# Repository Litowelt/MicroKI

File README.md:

# MicroKI

Das "MicroKI" ist ein Projekt, das sich mit digitalen Zusatzanzeigen befasst. Das MicroKI ermöglicht den Anschluss von bis zu 6 Zusatzanzeigen (0.96" OLED LCDs) an ein System. Die Daten für diese Anzeigen können entweder über den CAN-Bus (1x) oder über externe Sensor-Eingänge bezogen werden. Es stehen verschiedene externe Sensor-Eingänge zur Verfügung, darunter Batterie Spannung und Öldruck. Jede der 6 Anzeigen kann separat angesteuert werden und die Daten können über Tasten auf der Platine oder externe Tasten umgeschaltet werden.

# Anschluss Übersicht
Digitale Zusatzanzeigen (0.96" OLED LCDs):

- Bis zu 6 dieser Displays können an das MicroKI angeschlossen werden.

Datenquelle:

- Die Daten können über den CAN-Bus (1x) oder über externe Sensor-Eingänge bezogen werden.
  
Externe Sensor-Eingänge:

- 1x Batterie Spannung
- 1x Öldruck Sensor (VDO)
  
Steuerung und Umschaltung:

- Alle 6 Anzeigen können separat angesteuert werden.
- Die Umschaltung zwischen den Anzeigen und die Steuerung erfolgen entweder über die Buttons auf der Platine oder über externe Buttons.

# Unterstütze Fahrzeuge und Nachrichten

- VW T5.1
  - Öl Temperatur (wenn der Sensor verbaut ist) - ✓
  - Kühlwasser Temperatur - ✓
  - Ladeluft Temperatur - ✓
  - Außentemperatur (wenn der Sensor verbaut ist) - ✓
  - Ladedruck - ✓
 
- Universal (Analoge Eingänge)
  - Öl Temperatur - X
  - Kühlwasser Temperatur - X
  - Außentemperatur - X
  - Öldruck - X
  - Ladedruck - X
 
# ToDo
- Code fertig schreiben. - in Arbeit
- Prototypen V2 bauen (Bauteile und Platinen sind bestellt).
- CAN Nachrichten für T5.2 heraus finden. - Müssen nur noch final getestet werden
- CAN Support für Haltech ECU hinzufügen - in Arbeit
- CAN Support für Ecumaster EMU ECU hinzufügen - in Arbeit
- CAN Support für Maxx ECU hinzufügen - in Arbeit

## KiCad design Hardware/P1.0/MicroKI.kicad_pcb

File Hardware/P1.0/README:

This is just a prototype! I make no guarantees that it works. Use at your own risk!

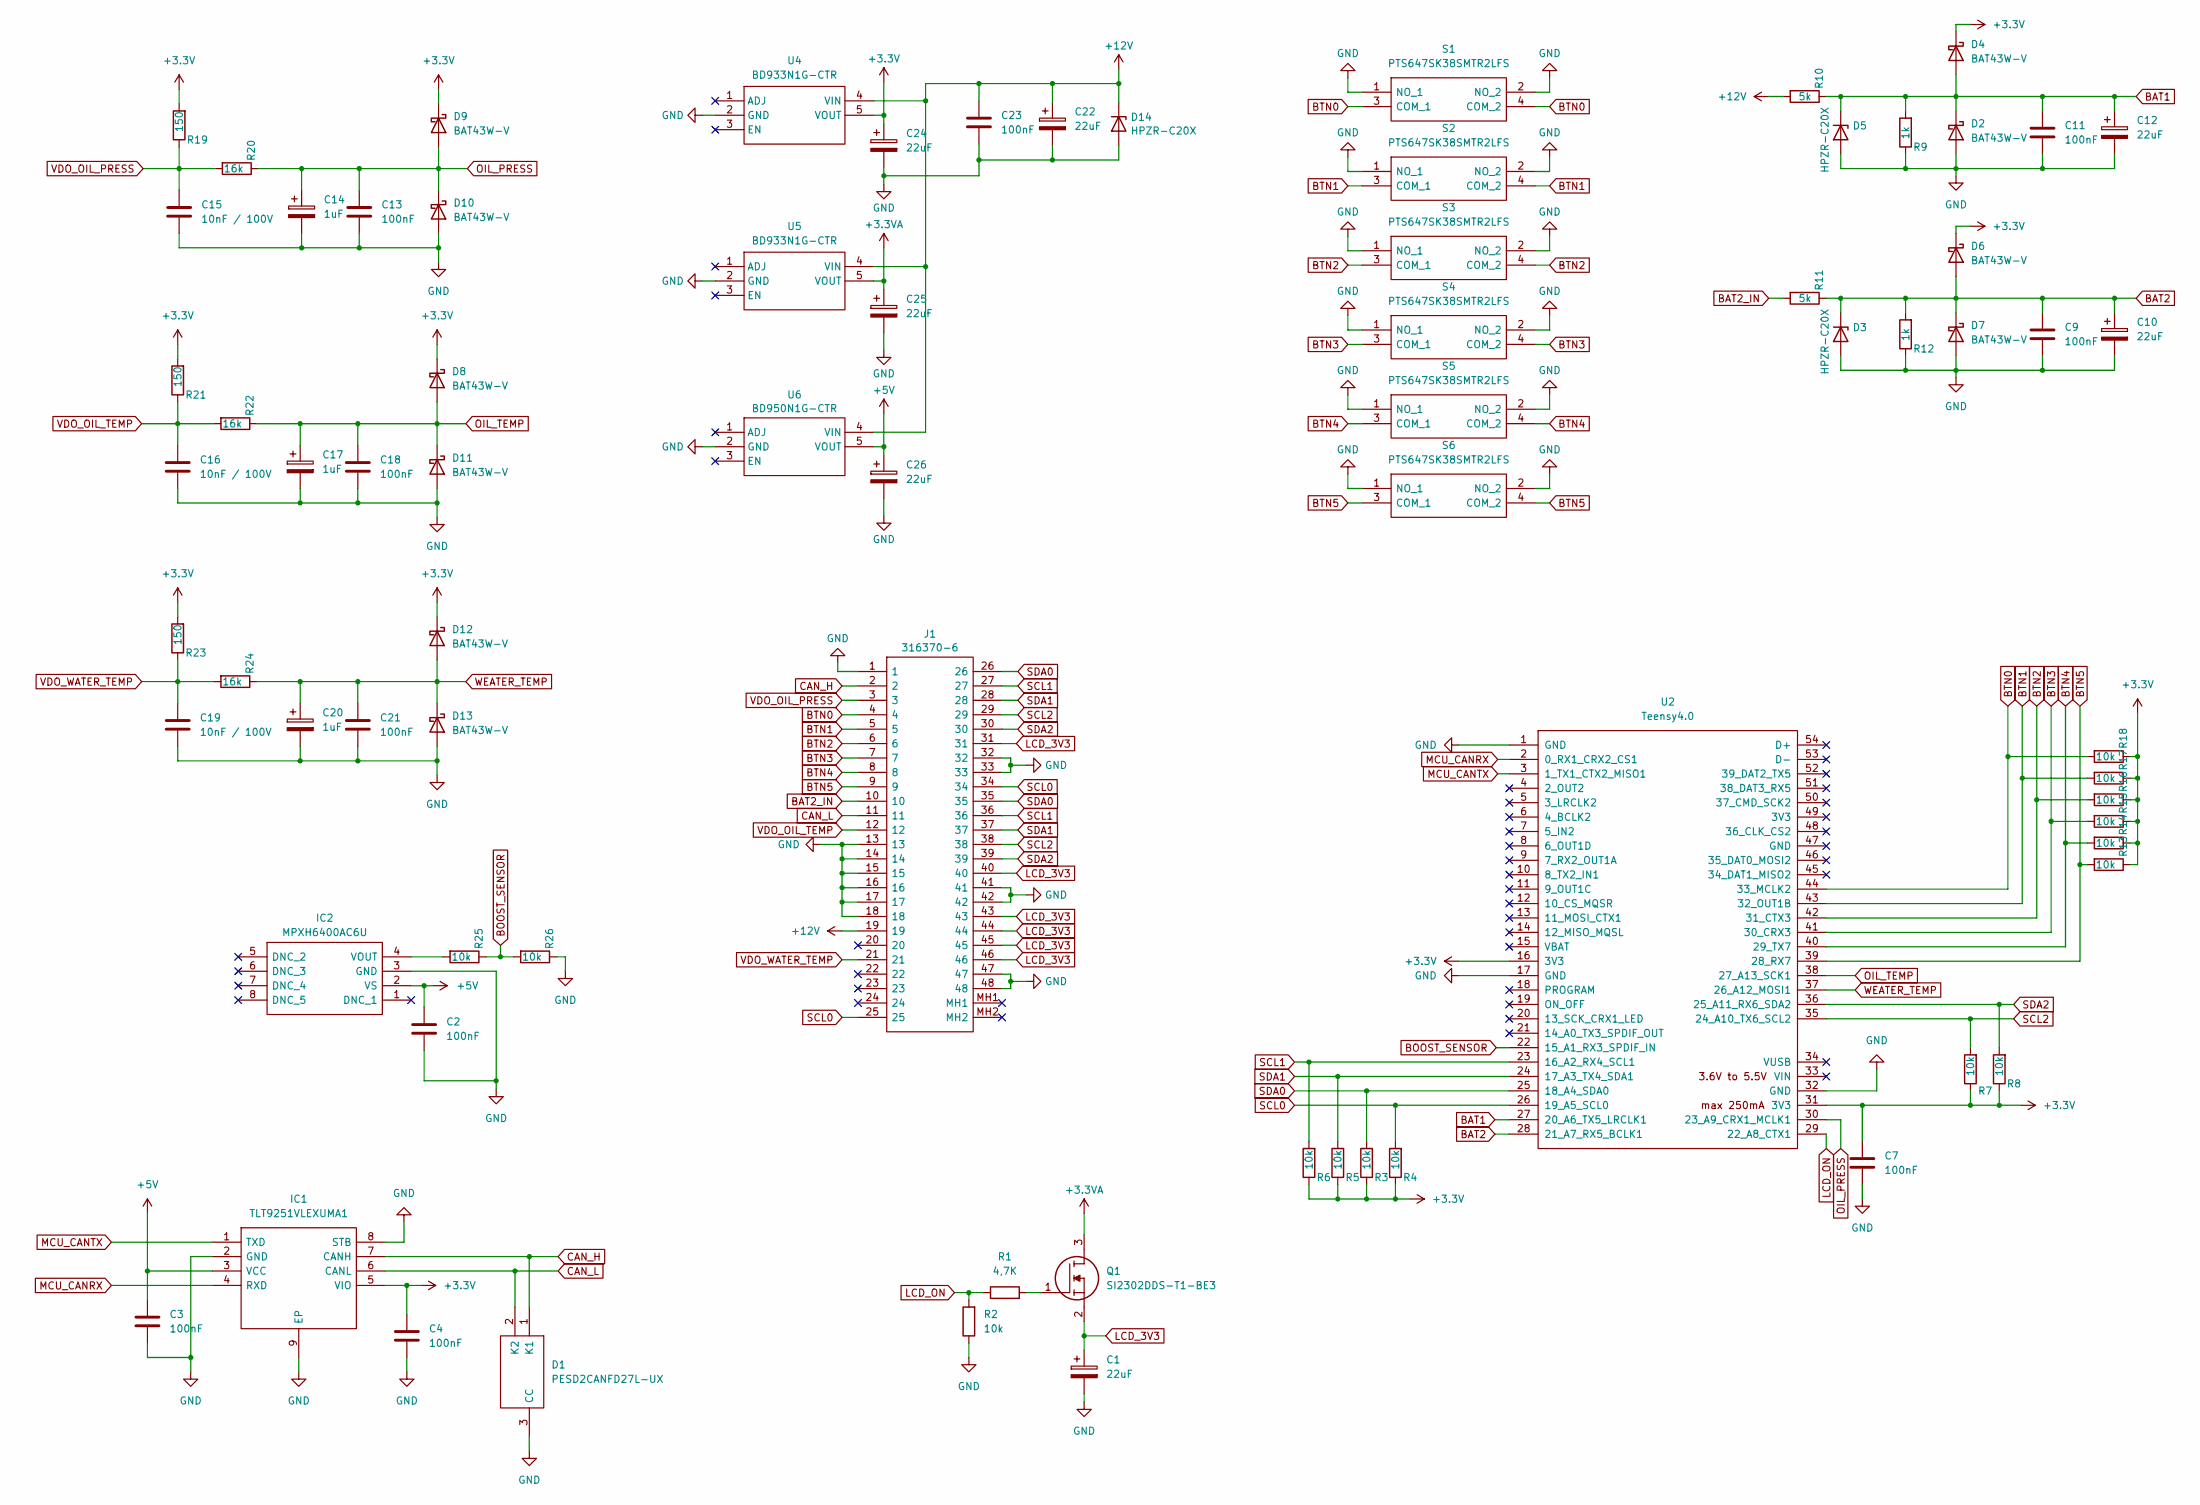
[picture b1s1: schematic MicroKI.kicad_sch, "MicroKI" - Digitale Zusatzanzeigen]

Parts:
C1, C10, C12, C22, C24, C25, C26: 22uF; CP_Elec_5x5.4; Manufacturer_Part_Number 865080442004; Mouser Part Number 710-865080442004
C2, C3, C4, C7, C9, C11, C13, C18, C21, C23: 100nF; C_0805_2012Metric_Pad1.18x1.45mm_HandSolder; Manufacturer_Part_Number C0805C104M5RAC7025; Mouser Part Number 80-C0805C104M5RACTM
C14, C17, C20: 1uF; CP_Elec_4x5.7; Manufacturer_Part_Number 865060640001; Mouser Part Number 710-865060640001
C15, C16, C19: 10nF / 100V; C_0603_1608Metric_Pad1.08x0.95mm_HandSolder; Manufacturer_Part_Number GCM188R72A103KA37J; Mouser Part Number 81-GCM188R72A103KA7J
D1: PESD2CANFD27L-UX; SOT65P210X110-3N; Mouser Part Number 771-PESD2CANFD27L-UX
D2, D4, D6, D7, D8, D9, D10, D11, D12, D13: BAT43W-V; D_SOD-123; Manufacturer_Part_Number BAT43W-G3-08; Mouser Part Number 78-BAT43W-G3-08
D3, D5, D14: HPZR-C20X; HPZRC20X; Manufacturer_Part_Number HPZR-C20X; Mouser Part Number 771-HPZR-C20X
IC1: TLT9251VLEXUMA1; SON65P300X300X110-9N; Manufacturer_Part_Number TLT9251VLEXUMA1; Mouser Part Number 726-TLT9251VLEXUMA1
IC2: MPXH6400AC6U; MPXH6115AC6U; Mouser Part Number 841-MPXH6400AC6U
J1: 316370-6; 3163706; Mouser Part Number 571-316370-6
Q1: SI2302DDS-T1-BE3; SOT95P237X112-3N; Mouser Part Number 78-SI2302DDS-T1-BE3
R1: 4,7K; R_0805_2012Metric_Pad1.20x1.40mm_HandSolder; Manufacturer_Part_Number RK73B2ATTD472J; Mouser Part Number 660-RK73B2ATTD472J
R2, R3, R4, R5, R6, R7, R8, R13, R14, R15, R16, R17, R18, R25, R26: 10k; R_0805_2012Metric_Pad1.20x1.40mm_HandSolder; Manufacturer_Part_Number RC0805FR-1010KL; Mouser Part Number 603-RC0805FR-1010KL
R9, R12: 1k; R_0805_2012Metric_Pad1.20x1.40mm_HandSolder; Manufacturer_Part_Number ERJ-P06D1001V; Mouser Part Number 667-ERJ-P06D1001V
R10, R11: 5k; R_0805_2012Metric_Pad1.20x1.40mm_HandSolder; Manufacturer_Part_Number CRCW08055K00FKTA; Mouser Part Number 71-CRCW0805-5K
R19, R21, R23: 150; R_0805_2012Metric_Pad1.20x1.40mm_HandSolder; Manufacturer_Part_Number ERJ-P06D1500V; Mouser Part Number 667-ERJ-P06D1500V
R20, R22, R24: 16k; R_0805_2012Metric_Pad1.20x1.40mm_HandSolder; Manufacturer_Part_Number RC0805FR-0716KL; Mouser Part Number 603-RC0805FR-0716KL
S1, S2, S3, S4, S5, S6: PTS647SK38SMTR2LFS; Mouser Part Number 611-PTS647SK38SMTR2L
U2: Teensy4.0; Teensy40_SMT
U4, U5: BD933N1G-CTR; BD9xxN1WG-CTR; Manufacturer_Part_Number BD933N1G-CTR; Mouser Part Number 755-BD933N1G-CTR
U6: BD950N1G-CTR; BD9xxN1WG-CTR; Manufacturer_Part_Number BD950N1G-CTR; Mouser Part Number 755-BD950N1G-CTR

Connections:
+3.3V: C4.1, C7.1, C24.1, D4.1 (K), D6.1 (K), D8.1 (K), D9.1 (K), D12.1 (K), IC1.5 (VIO), R3.1, R4.1, R5.1, R6.1, R7.1, R8.1, R13.1, R14.1, R15.1, R16.1, R17.1, R18.1, R19.2, R21.2, R23.2, U2.16 (3V3), U2.31 (3V3), U4.5 (VOUT)
+3.3VA: C25.1, Q1.3, U5.5 (VOUT)
+5V: C2.1, C3.1, C26.1, IC1.3 (VCC), IC2.2 (VS), U6.5 (VOUT)
+12V: C22.1, C23.1, D14.1 (K), J1.19, R10.2, U4.4 (VIN), U5.4 (VIN), U6.4 (VIN)
BAT1: C11.1, C12.1, D2.1 (K), D4.2 (A), D5.1 (K), R9.2, R10.1, U2.27 (20_A6_TX5_LRCLK1)
BAT2: C9.1, C10.1, D3.1 (K), D6.2 (A), D7.1 (K), R11.1, R12.2, U2.28 (21_A7_RX5_BCLK1)
BAT2_IN: J1.10, R11.2
BOOST_SENSOR: R25.1, R26.2, U2.22 (15_A1_RX3_SPDIF_IN)
BTN0: J1.4, R18.2, S1.3 (COM_1), S1.4 (COM_2), U2.44 (33_MCLK2)
BTN1: J1.5, R17.2, S2.3 (COM_1), S2.4 (COM_2), U2.43 (32_OUT1B)
BTN2: J1.6, R16.2, S3.3 (COM_1), S3.4 (COM_2), U2.42 (31_CTX3)
BTN3: J1.7, R15.2, S4.3 (COM_1), S4.4 (COM_2), U2.41 (30_CRX3)
BTN4: J1.8, R14.2, S5.3 (COM_1), S5.4 (COM_2), U2.40 (29_TX7)
BTN5: J1.9, R13.2, S6.3 (COM_1), S6.4 (COM_2), U2.39 (28_RX7)
CAN_H: D1.1 (K1), IC1.7 (CANH), J1.2
CAN_L: D1.2 (K2), IC1.6 (CANL), J1.11
GND: C1.2, C2.2, C3.2, C4.2, C7.2, C9.2, C10.2, C11.2, C12.2, C13.2, C14.2, C15.2, C16.2, C17.2, C18.2, C19.2, C20.2, C21.2, C22.2, C23.2, C24.2, C25.2, C26.2, D1.3 (CC), D2.2 (A), D3.2 (A), D5.2 (A), D7.2 (A), D10.2 (A), D11.2 (A), D13.2 (A), D14.2 (A), IC1.2 (GND), IC1.8 (STB), IC1.9 (EP), IC2.3 (GND), J1.1, J1.13, J1.14, J1.15, J1.16, J1.17, J1.18, J1.32, J1.33, J1.41, J1.42, J1.47, J1.48, R2.1, R9.1, R12.1, R26.1, S1.1 (NO_1), S1.2 (NO_2), S2.1 (NO_1), S2.2 (NO_2), S3.1 (NO_1), S3.2 (NO_2), S4.1 (NO_1), S4.2 (NO_2), S5.1 (NO_1), S5.2 (NO_2), S6.1 (NO_1), S6.2 (NO_2), U2.1 (GND), U2.17 (GND), U2.32 (GND), U4.2 (GND), U5.2 (GND), U6.2 (GND)
LCD_3V3: C1.1, J1.31, J1.40, J1.43, J1.44, J1.45, J1.46, Q1.2
LCD_ON: R1.1, R2.2, U2.29 (22_A8_CTX1)
MCU_CANRX: IC1.4 (RXD), U2.2 (0_RX1_CRX2_CS1)
MCU_CANTX: IC1.1 (TXD), U2.3 (1_TX1_CTX2_MISO1)
unnamed: IC2.4 (VOUT), R25.2
unnamed: Q1.1, R1.2
OIL_PRESS: C13.1, C14.1, D9.2 (A), D10.1 (K), R20.1, U2.30 (23_A9_CRX1_MCLK1)
OIL_TEMP: C17.1, C18.1, D8.2 (A), D11.1 (K), R22.1, U2.38 (27_A13_SCK1)
SCL0: J1.25, J1.34, R4.2, U2.26 (19_A5_SCL0)
SCL1: J1.27, J1.36, R6.2, U2.23 (16_A2_RX4_SCL1)
SCL2: J1.29, J1.38, R7.2, U2.35 (24_A10_TX6_SCL2)
SDA0: J1.26, J1.35, R3.2, U2.25 (18_A4_SDA0)
SDA1: J1.28, J1.37, R5.2, U2.24 (17_A3_TX4_SDA1)
SDA2: J1.30, J1.39, R8.2, U2.36 (25_A11_RX6_SDA2)
VDO_OIL_PRESS: C15.1, J1.3, R19.1, R20.2
VDO_OIL_TEMP: C16.1, J1.12, R21.1, R22.2
VDO_WATER_TEMP: C19.1, J1.21, R23.1, R24.2
WEATER_TEMP: C20.1, C21.1, D12.2 (A), D13.1 (K), R24.1, U2.37 (26_A12_MOSI1)

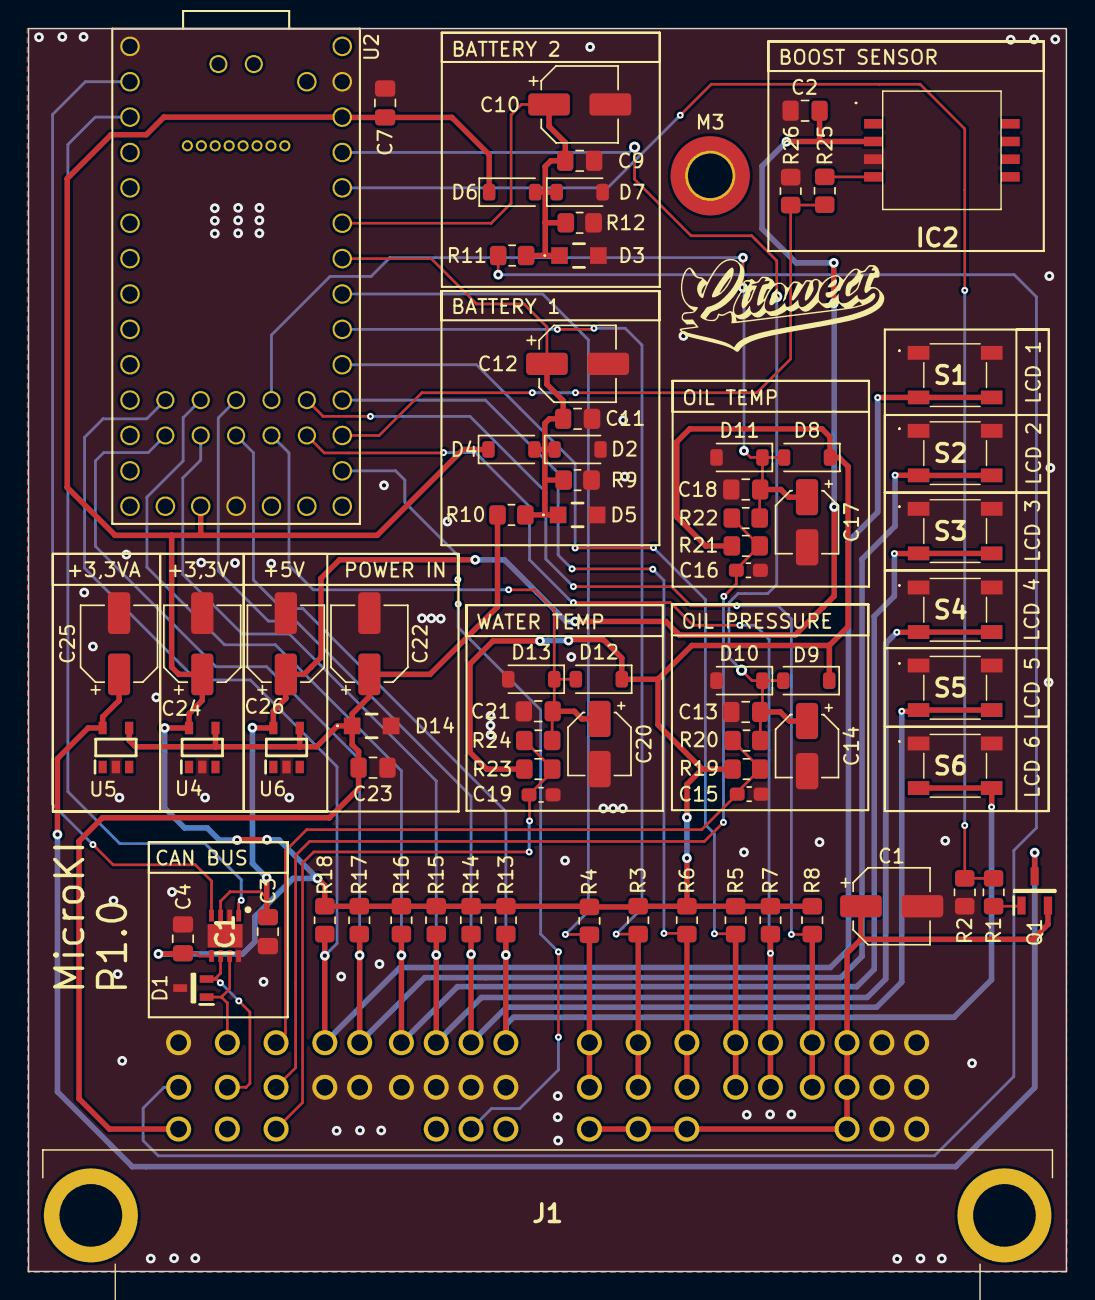
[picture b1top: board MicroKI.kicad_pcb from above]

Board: 2 copper layers, 74.5 x 89.3 mm, 78 parts (0 on the bottom side), 35 nets.

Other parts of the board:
M3: MountingHole_3.2mm_M3_ISO7380_Pad_TopBottom

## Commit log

2023-11-07 Create Prototype
2023-11-07 Create _
2023-11-08 Change License
2023-11-08 Create LICENSE
2023-11-08 Uploaded Prototype V. P1.0
    This is just a prototype! I make no guarantees that it works. Use at your own risk!
2023-11-08 README
2023-11-08 Added gerber files
2023-12-09 Add files via upload
    Prototyp Version 1.1 - NICHT GETESTET
2024-02-17 Create P1.4 only CAN ESP32
